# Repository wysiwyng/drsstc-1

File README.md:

# drsstc-1
my shot at a drsstc
expect eagle files for driver, power inverter and interrupter as well as code for said interrupter soon

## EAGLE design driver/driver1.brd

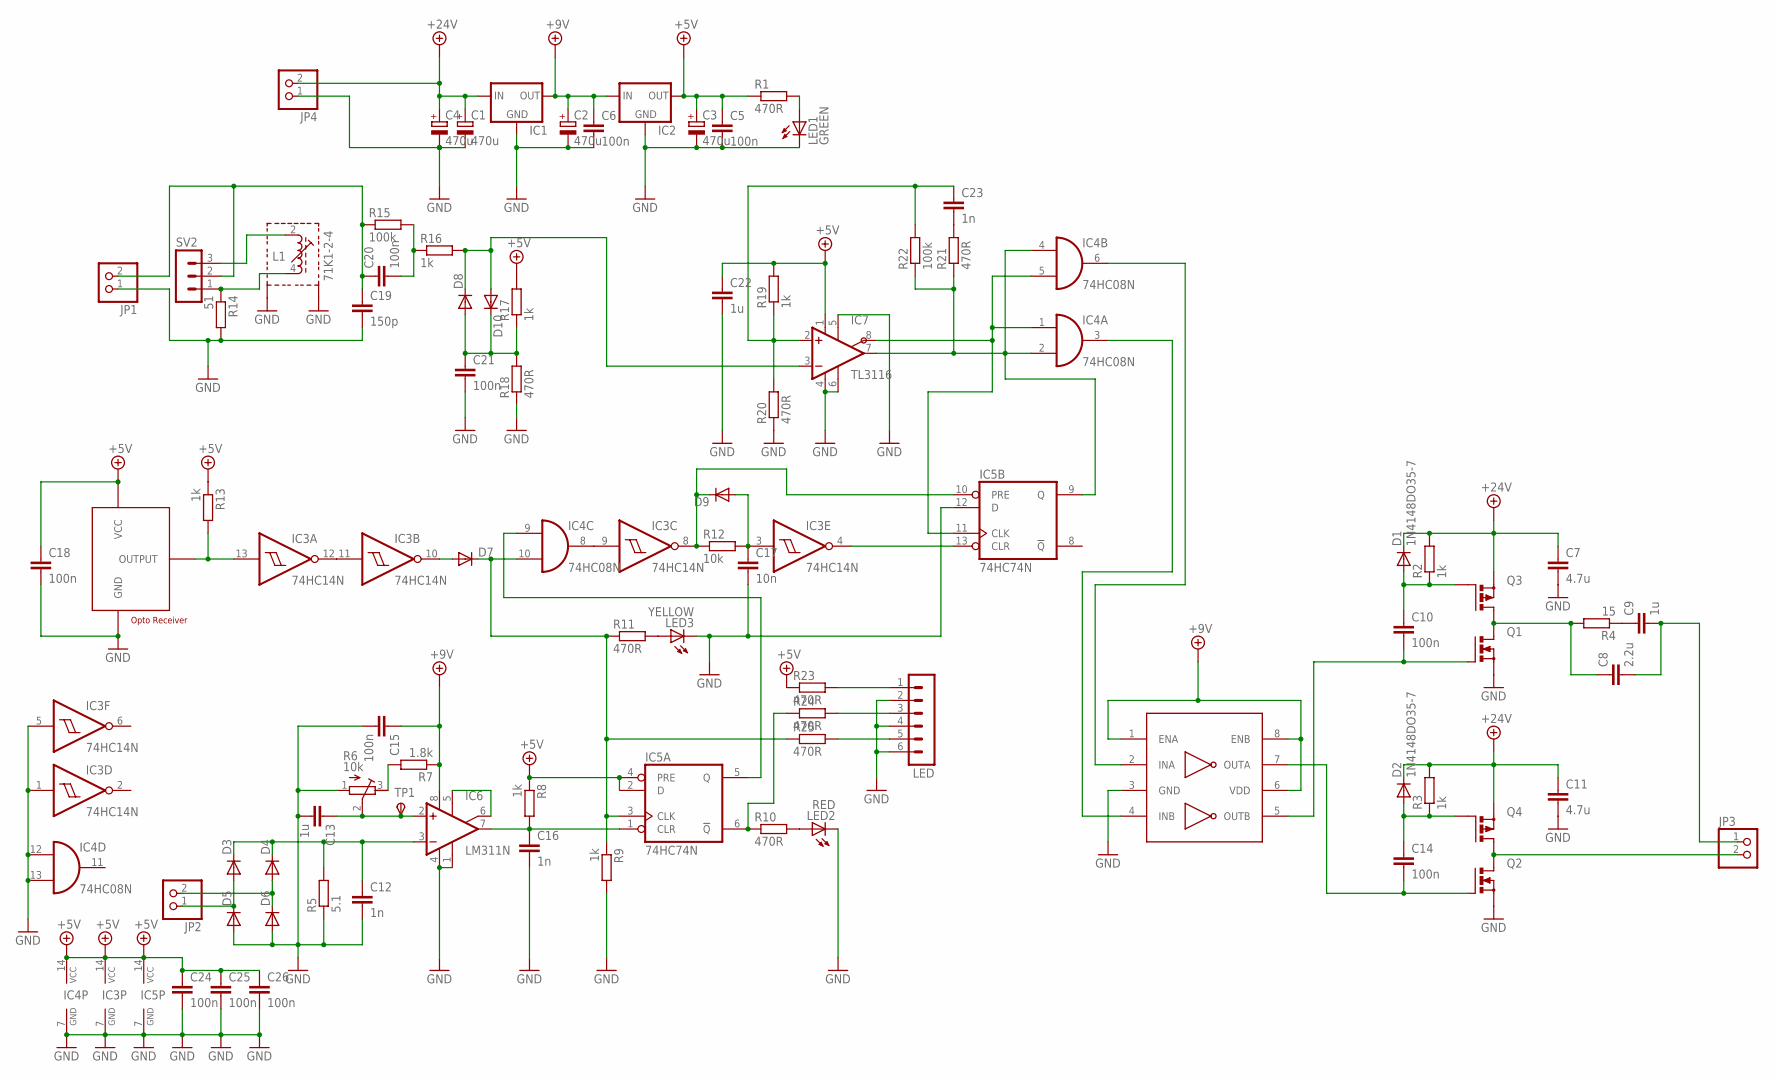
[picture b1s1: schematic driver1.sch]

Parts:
C1, C2, C3, C4: 470u; E5-8,5
C5, C6, C10, C14, C15, C18, C20, C21, C24, C25, C26: 100n; C025-025X050
C7, C11: 4.7u; C025-025X050
C8: 2.2u; C025-025X050
C9, C13, C22: 1u; C025-025X050
C12, C16, C23: 1n; C025-025X050
C17: 10n; C025-025X050
C19: 150p; C025-025X050
D1, D2: 1N4148DO35-7; DO35-7
D3, D4, D5, D6, D7, D8, D9, D10: DIODE-D-7.5; D-7.5
IC1, IC2: 78XXS
IC3: 74HC14N; DIL14
IC4: 74HC08N; DIL14
IC5: 74HC74N; DIL14
IC6: LM311N; DIL8
IC7: TL3116; DIL8
IC8: UCC27423; DIL8
JP1, JP2, JP3, JP4: PINHD-1X2; 1X02
L1: 71K1-2-4; 71K
LED: MA06-1
LED1: GREEN; LED3MM
LED2: RED; LED3MM
LED3: YELLOW; LED3MM
OP1: IFD95; OPTO-RECEIVER
Q1, Q2: PMOSFET_NTO220BV; TO220BV
Q3, Q4: PMOSFET_PTO220BV; TO220BV
R1, R10, R11, R18, R20, R21, R23, R24, R25: 470R; 0207/7
R2, R3, R8, R9, R13, R16, R17, R19: 1k; 0207/7
R4: 15; 0207/7
R5: 5.1; 0309/12
R6: 10k; RTRIM64W
R7: 1.8k; 0207/7
R12: 10k; 0207/7
R14: 51; 0309/12
R15, R22: 100k; 0207/7
SV2: MA03-1
TP1: TPSTP20R; TP20R

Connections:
+5V: C3.+, C5.1, C18.1, C22.1, C24.1, C25.1, C26.1, IC2.OUT, IC3.14 (VCC), IC4.14 (VCC), IC5.2 (D), IC5.4 (PRE), IC5.14 (VCC), IC7.1 (V+), OP1.P$3 (VCC), R1.1, R8.1, R13.1, R17.2, R19.2, R23.1
+9V: C2.+, C6.1, C15.1, IC1.OUT, IC2.IN, IC6.8 (V+), IC8.1 (ENA), IC8.6 (VDD), IC8.8 (ENB), R7.1
+24V: C1.+, C4.+, C7.1, C11.1, D1.C, D2.C, IC1.IN, JP4.2, Q3.S, Q4.S, R2.2, R3.2
GND: C1.-, C2.-, C3.-, C4.-, C5.2, C6.2, C7.2, C11.2, C12.2, C13.2, C15.2, C16.2, C17.2, C18.2, C19.2, C21.2, C22.2, C24.2, C25.2, C26.2, D5.A, D6.A, IC1.GND, IC2.GND, IC3.1 (I), IC3.5 (I), IC3.7 (GND), IC4.7 (GND), IC4.12 (I0), IC4.13 (I1), IC5.7 (GND), IC5.12 (D), IC6.1 (GND), IC6.4 (V-), IC7.4 (V-), IC7.5 (LEN), IC7.6 (GND), IC8.3 (GND), JP1.1, JP4.1, L1.S1, L1.S2, LED.2, LED.4, LED.6, LED1.K (C), LED2.K (C), LED3.K (C), OP1.P$1 (GND), Q1.S, Q2.S, R5.1, R6.1 (A), R9.2, R14.2, R18.1, R20.1
unnamed: IC3.11 (I), IC3.12 (O)
unnamed: LED1.A, R1.2
unnamed: IC3.9 (I), IC4.8 (O)
unnamed: C8.1, Q1.D, Q3.D, R4.2
unnamed: IC6.5 (ON), IC6.6 (ON/STR)
unnamed: C10.1, D1.A, Q3.G, R2.1
unnamed: IC4.2 (I1), IC4.4 (I0), IC5.9 (Q), IC7.7 (OUT), R21.1, R22.1
unnamed: C9.1, R4.1
unnamed: C8.2, C9.2, JP3.1
unnamed: C14.1, D2.A, Q4.G, R3.1
unnamed: IC4.6 (O), IC8.2 (INA)
unnamed: JP3.2, Q2.D, Q4.D
unnamed: C16.1, IC5.1 (CLR), IC6.7 (OUT), R8.2
unnamed: R6.3 (E), R7.2
unnamed: LED.1, R23.2
unnamed: LED.3, R24.2
unnamed: IC4.3 (O), IC8.4 (INB)
unnamed: LED.5, R25.2
unnamed: C13.1, IC6.2 (+IN), R6.2 (S), TP1.TP
unnamed: C12.1, D3.C, D4.C, IC6.3 (-IN), R5.2
unnamed: D9.C, IC3.8 (O), IC5.10 (PRE), R12.1
unnamed: D3.A, D5.C, JP2.1
unnamed: D4.A, D6.C, JP2.2
unnamed: D7.C, IC4.10 (I1), IC5.3 (CLK), R9.1, R11.1, R25.1
unnamed: IC3.13 (I), OP1.P$2 (OUTPUT), R13.2
unnamed: D7.A, IC3.10 (O)
unnamed: IC5.6 (!Q), R10.1, R24.1
unnamed: LED2.A, R10.2
unnamed: LED3.A, R11.2
unnamed: IC4.9 (I0), IC5.5 (Q)
unnamed: C17.1, D9.A, IC3.3 (I), R12.2
unnamed: IC3.4 (O), IC5.13 (CLR)
unnamed: IC4.1 (I0), IC4.5 (I1), IC5.11 (CLK), IC7.8 (!OUT)
unnamed: C19.1, C20.1, JP1.2, R15.1, SV2.2
unnamed: C14.2, IC8.7 (OUTA), Q2.G
unnamed: C20.2, R15.2, R16.1
unnamed: L1.4 (E), R14.1, SV2.1
unnamed: L1.2 (A), SV2.3
unnamed: D8.C, D10.A, IC7.3 (-IN), R16.2
unnamed: C21.1, D8.A, D10.C, R17.1, R18.2
unnamed: C10.2, IC8.5 (OUTB), Q1.G
unnamed: C23.2, R21.2
unnamed: C23.1, IC7.2 (+IN), R19.1, R20.2, R22.2

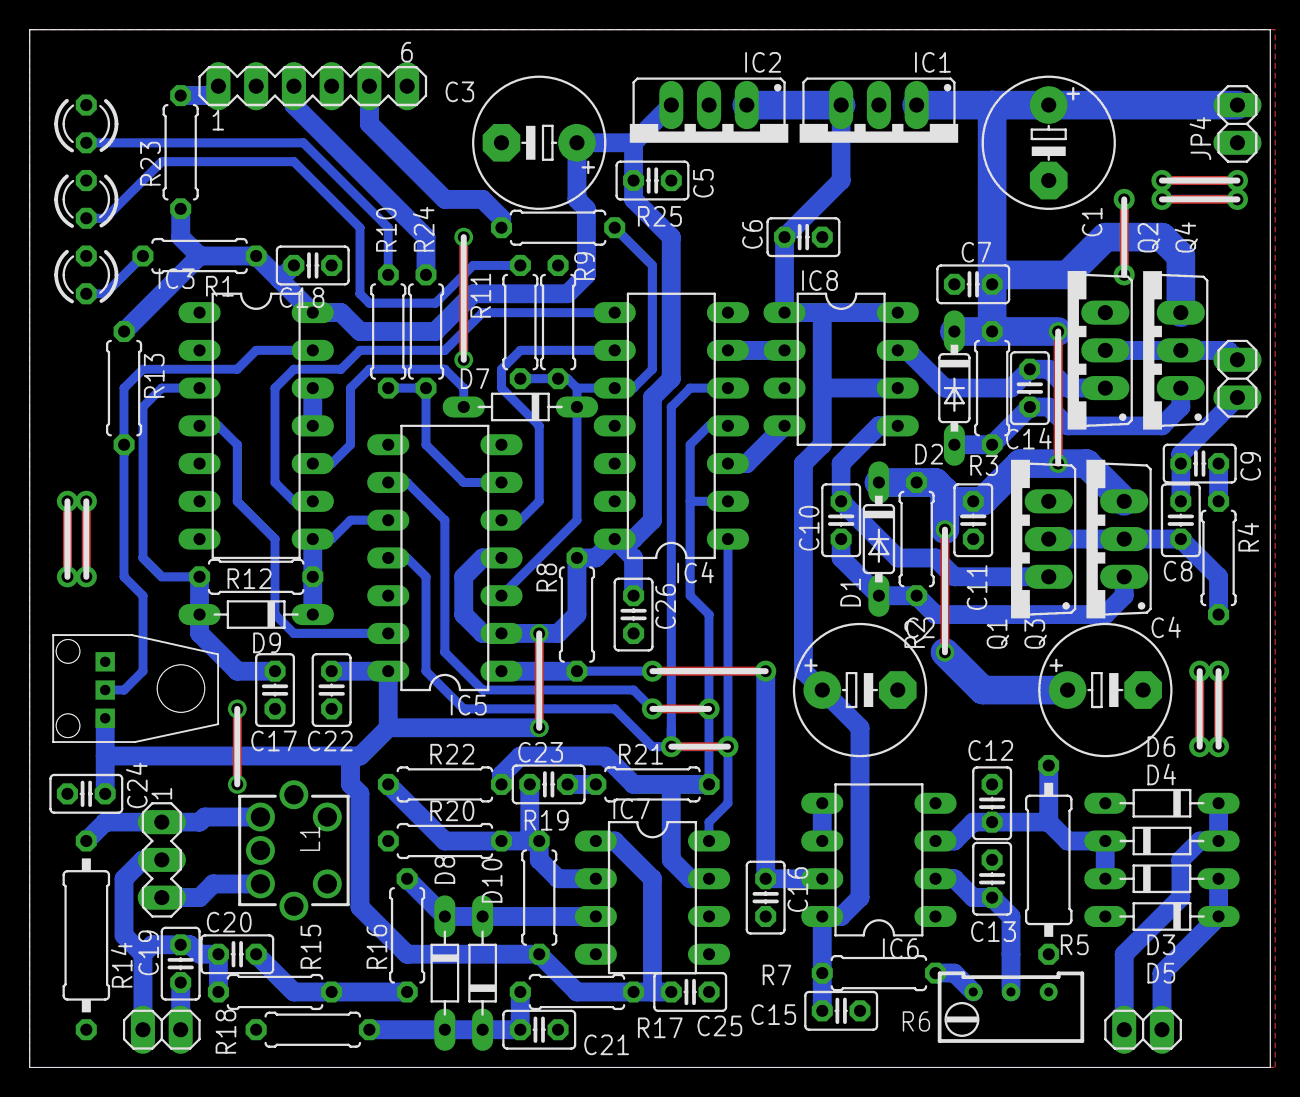
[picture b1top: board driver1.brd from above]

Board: 2 copper layers, 83.5 x 69.8 mm, 85 parts (1 on the bottom side), 47 nets.

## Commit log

2015-06-21 added eagle files
2015-06-21 moved driver files to seperate directory
2015-06-21 improved board layout for use with recom switching 78xx regulators
2015-06-22 further pcb optimizations
2015-06-23 guess what.. pcb improvements
2015-06-23 added part values
2015-06-23 added missing prefix to libraries
